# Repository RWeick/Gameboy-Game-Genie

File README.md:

# Gameboy-Game-Genie
The Kicad files and rom dump of the Gameboy Game Genie by Galoob. This includes the additional PCBs for the buttons and the LED.

In the replacement board folder, you will find a version of the PCB that uses an Atmel AT27C256 (or chip of compatible size and pinout) to replace the chip blob. This enables anyone with a damaged PCB to restore the system. It has been tested.

PCB Thicknesses: 0.8 mm

Replacement Board:

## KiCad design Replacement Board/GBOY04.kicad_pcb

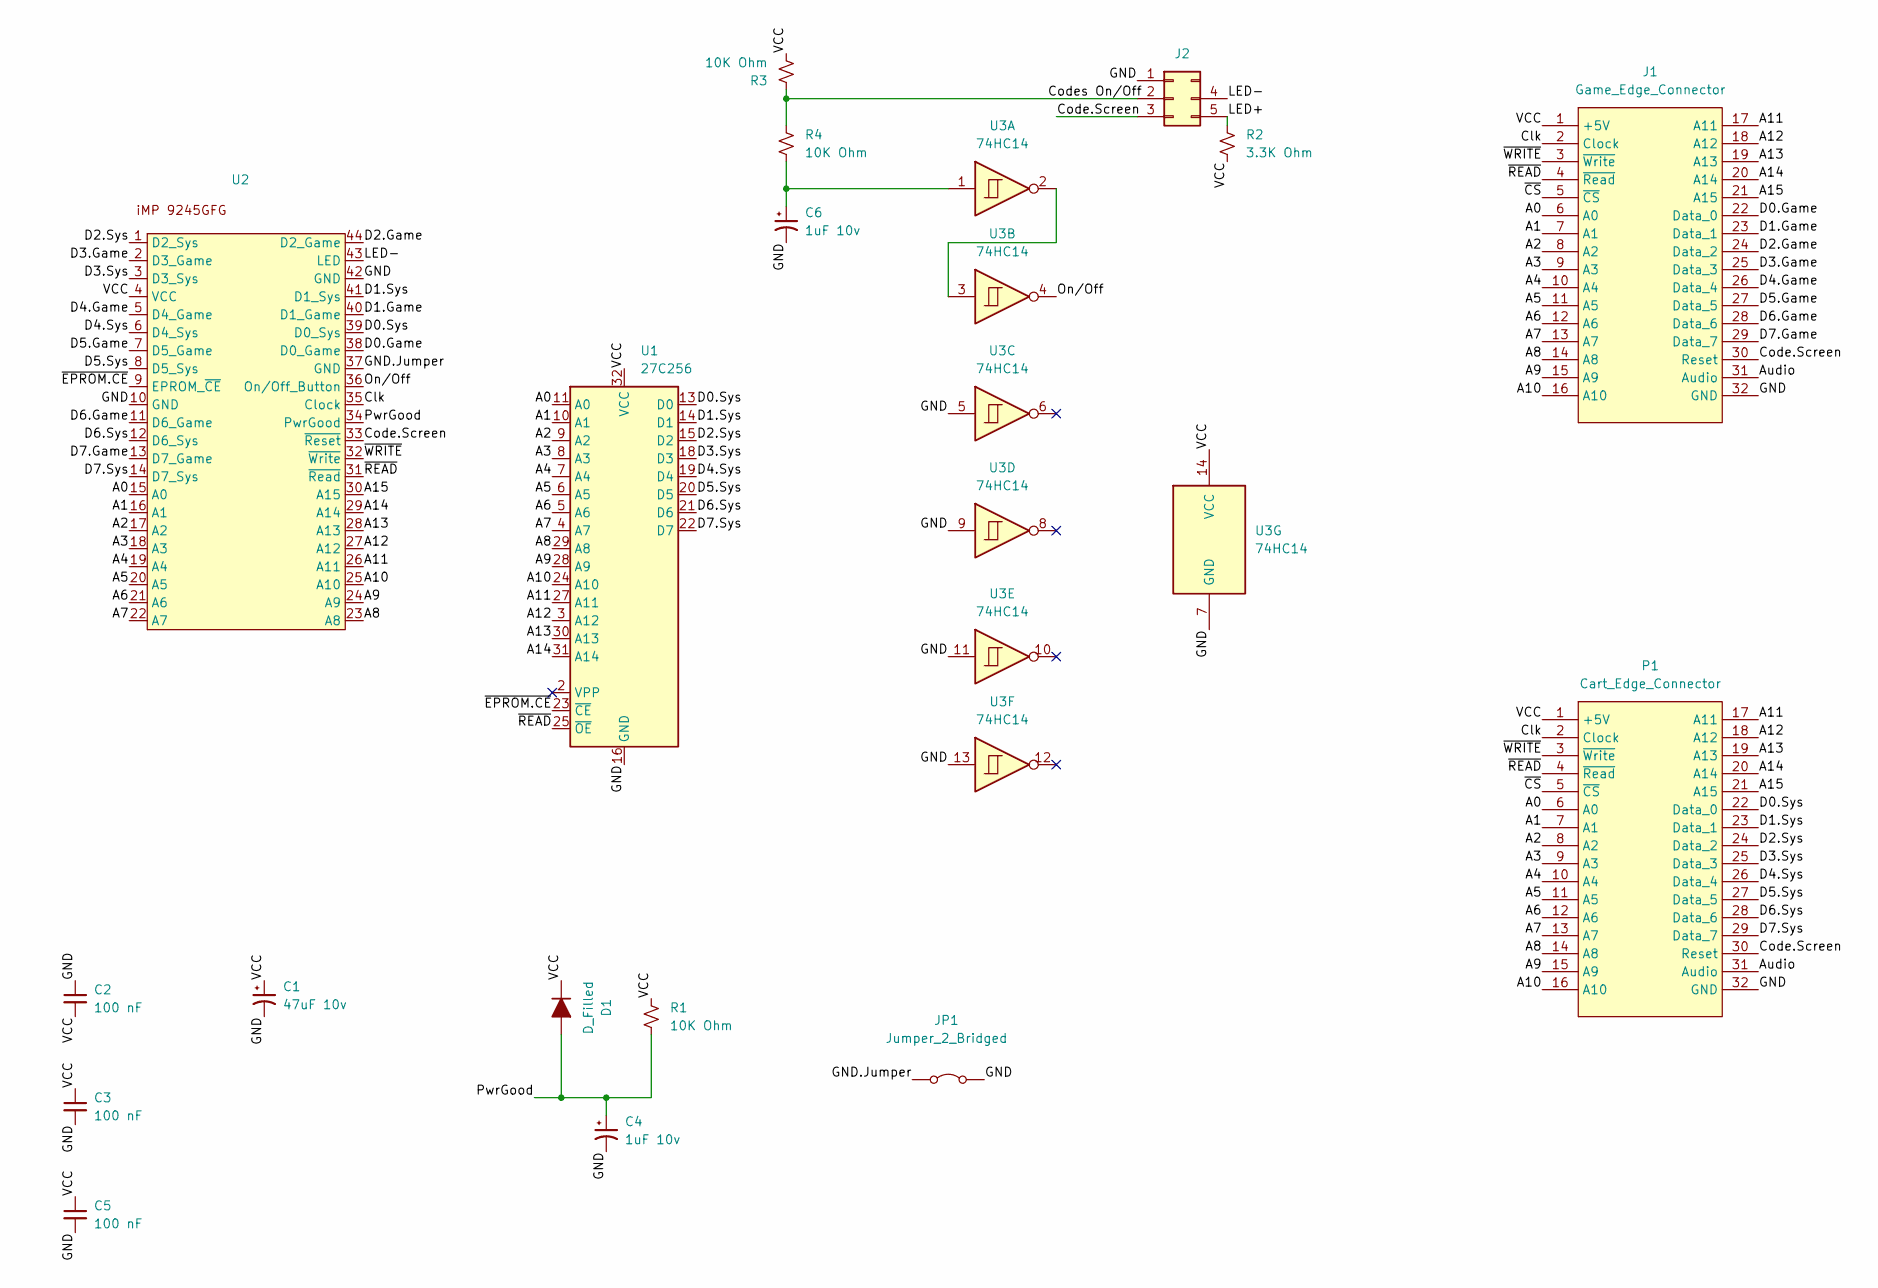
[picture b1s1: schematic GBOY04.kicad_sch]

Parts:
C1: 47uF 10v; C_Radial_D6.3mm_H5.0mm_P2.50mm
C2, C5: 100 nF; C_Disc_D5.0mm_W2.5mm_P5.00mm
C3: 100 nF; C_1206_3216Metric_Pad1.33x1.80mm_HandSolder
C4, C6: 1uF 10v; C_Disc_D3.8mm_W2.6mm_P2.50mm
D1: D_Filled; D_DO-35_SOD27_P7.62mm_Horizontal
J1: Game_Edge_Connector; Cartridge Connector
J2: Conn_02x03_Counter_Clockwise; PinHeader_2x03_P2.54mm_Vertical
JP1: Jumper_2_Bridged; SolderJumper-2_P1.3mm_Open_RoundedPad1.0x1.5mm
P1: Cart_Edge_Connector; Edge Connector
R1, R3, R4: 10K Ohm; R_Axial_DIN0204_L3.6mm_D1.6mm_P7.62mm_Horizontal
R2: 3.3K Ohm; R_Axial_DIN0204_L3.6mm_D1.6mm_P7.62mm_Horizontal
U1: 27C256; EPROM
U2: iMP PLD
U3: 74HC14; DIP-14_W7.62mm

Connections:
/A0: J1.6 (A0), P1.6 (A0), U1.11 (A0), U2.15 (A0)
/A1: J1.7 (A1), P1.7 (A1), U1.10 (A1), U2.16 (A1)
/A2: J1.8 (A2), P1.8 (A2), U1.9 (A2), U2.17 (A2)
/A3: J1.9 (A3), P1.9 (A3), U1.8 (A3), U2.18 (A3)
/A4: J1.10 (A4), P1.10 (A4), U1.7 (A4), U2.19 (A4)
/A5: J1.11 (A5), P1.11 (A5), U1.6 (A5), U2.20 (A5)
/A6: J1.12 (A6), P1.12 (A6), U1.5 (A6), U2.21 (A6)
/A7: J1.13 (A7), P1.13 (A7), U1.4 (A7), U2.22 (A7)
/A8: J1.14 (A8), P1.14 (A8), U1.29 (A8), U2.23 (A8)
/A9: J1.15 (A9), P1.15 (A9), U1.28 (A9), U2.24 (A9)
/A10: J1.16 (A10), P1.16 (A10), U1.24 (A10), U2.25 (A10)
/A11: J1.17 (A11), P1.17 (A11), U1.27 (A11), U2.26 (A11)
/A12: J1.18 (A12), P1.18 (A12), U1.3 (A12), U2.27 (A12)
/A13: J1.19 (A13), P1.19 (A13), U1.30 (A13), U2.28 (A13)
/A14: J1.20 (A14), P1.20 (A14), U1.31 (A14), U2.29 (A14)
/A15: J1.21 (A15), P1.21 (A15), U2.30 (A15)
/Audio: J1.31 (Audio), P1.31 (Audio)
/Clk: J1.2 (Clock), P1.2 (Clock), U2.35 (Clock)
/Code.Screen: J1.30 (Reset), J2.3, P1.30 (Reset), U2.33 (~Reset)
/Codes On/Off: J2.2, R3.1, R4.1
/D0.Game: J1.22 (Data_0), U2.38 (D0_Game)
/D0.Sys: P1.22 (Data_0), U1.13 (D0), U2.39 (D0_Sys)
/D1.Game: J1.23 (Data_1), U2.40 (D1_Game)
/D1.Sys: P1.23 (Data_1), U1.14 (D1), U2.41 (D1_Sys)
/D2.Game: J1.24 (Data_2), U2.44 (D2_Game)
/D2.Sys: P1.24 (Data_2), U1.15 (D2), U2.1 (D2_Sys)
/D3.Game: J1.25 (Data_3), U2.2 (D3_Game)
/D3.Sys: P1.25 (Data_3), U1.18 (D3), U2.3 (D3_Sys)
/D4.Game: J1.26 (Data_4), U2.5 (D4_Game)
/D4.Sys: P1.26 (Data_4), U1.19 (D4), U2.6 (D4_Sys)
/D5.Game: J1.27 (Data_5), U2.7 (D5_Game)
/D5.Sys: P1.27 (Data_5), U1.20 (D5), U2.8 (D5_Sys)
/D6.Game: J1.28 (Data_6), U2.11 (D6_Game)
/D6.Sys: P1.28 (Data_6), U1.21 (D6), U2.12 (D6_Sys)
/D7.Game: J1.29 (Data_7), U2.13 (D7_Game)
/D7.Sys: P1.29 (Data_7), U1.22 (D7), U2.14 (D7_Sys)
/GND: C1.2, C2.1, C3.2, C4.2, C5.2, C6.2, J1.32 (GND), J2.1, JP1.2 (B), P1.32 (GND), U1.16 (GND), U2.10 (GND), U2.42 (GND), U3.5, U3.7 (GND), U3.9, U3.11, U3.13
/GND.Jumper: JP1.1 (A), U2.37 (GND)
/LED+: J2.5, R2.1
/LED-: J2.4, U2.43 (LED)
/On/Off: U2.36 (On/Off_Button), U3.4
/PwrGood: C4.1, D1.2 (A), R1.2, U2.34 (PwrGood)
/VCC: C1.1, C2.2, C3.1, C5.1, D1.1 (K), J1.1 (+5V), P1.1 (+5V), R1.1, R2.2, R3.2, U1.32 (VCC), U2.4 (VCC), U3.14 (VCC)
/~CS: J1.5 (~CS), P1.5 (~CS)
/~EPROM.CE: U1.23 (~CE), U2.9 (EPROM_~CE)
/~READ: J1.4 (~Read), P1.4 (~Read), U1.25 (~OE), U2.31 (~Read)
/~WRITE: J1.3 (~Write), P1.3 (~Write), U2.32 (~Write)
unnamed: C6.1, R4.2, U3.1
unnamed: U3.2, U3.3

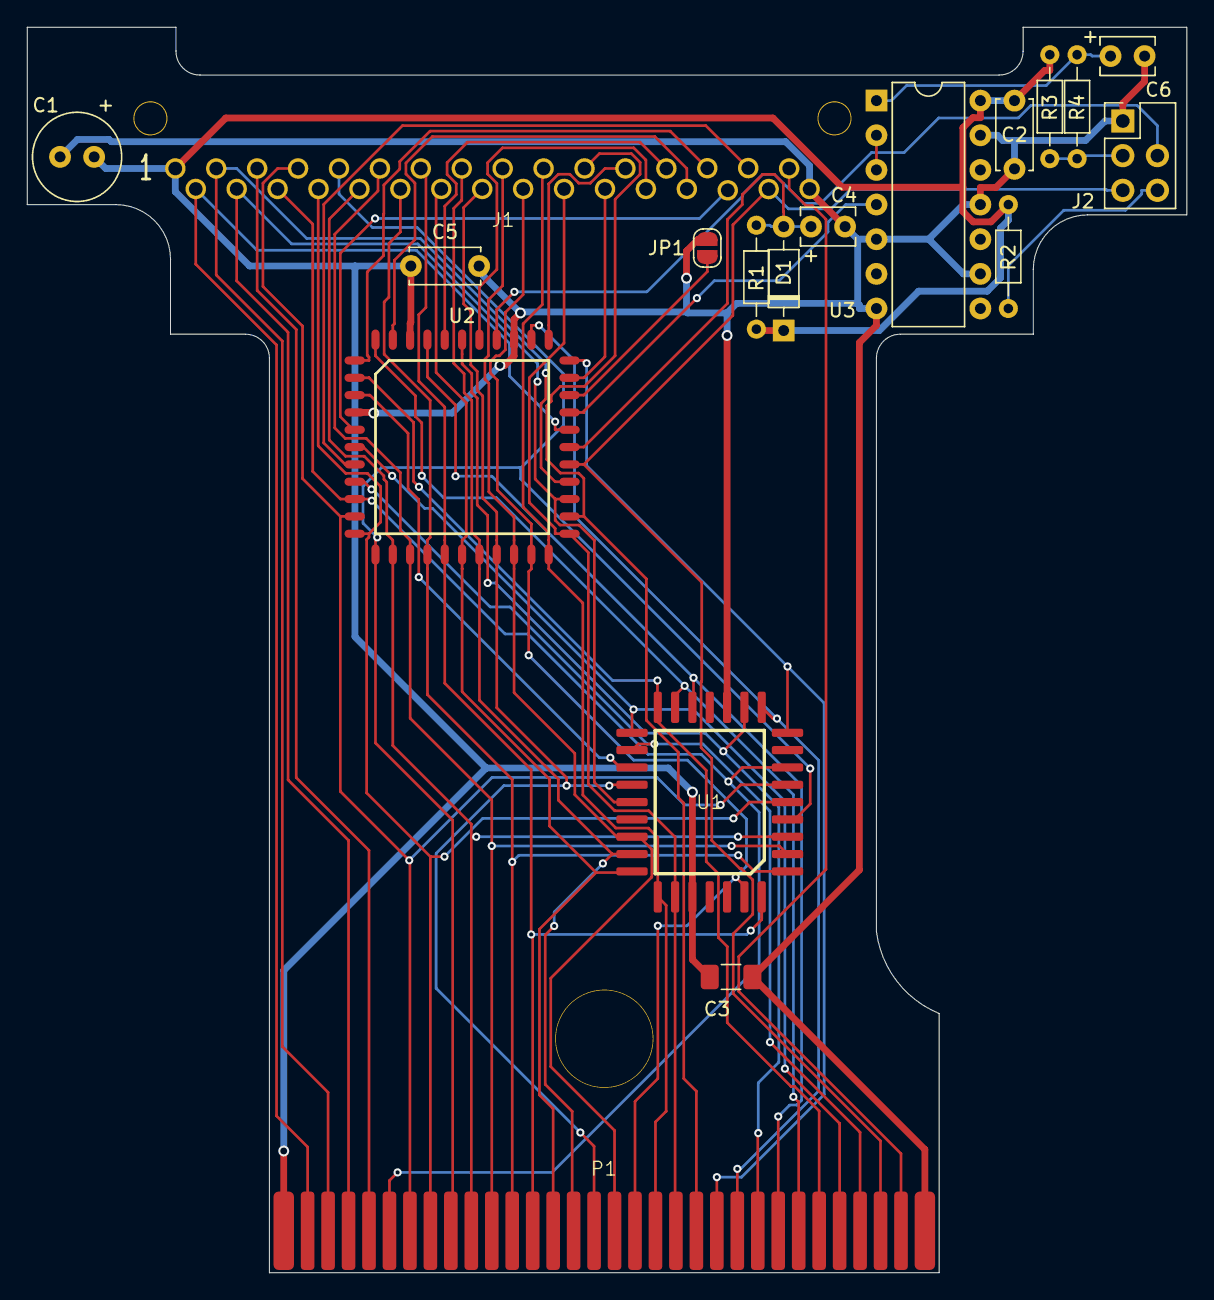
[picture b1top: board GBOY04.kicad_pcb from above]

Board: 2 copper layers, 85.0 x 91.3 mm, 19 parts (0 on the bottom side), 49 nets.

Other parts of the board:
Hole: Drill Hole

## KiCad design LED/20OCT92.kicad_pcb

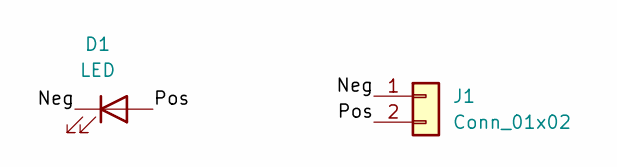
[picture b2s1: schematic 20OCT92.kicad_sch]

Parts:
D1: LED; LED_D4.0mm
J1: Conn_01x02; PinHeader_1x02_P2.54mm_Vertical

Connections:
/Neg: D1.1 (K), J1.1
/Pos: D1.2 (A), J1.2

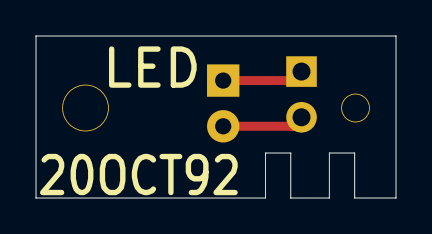
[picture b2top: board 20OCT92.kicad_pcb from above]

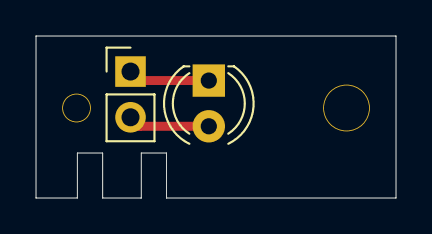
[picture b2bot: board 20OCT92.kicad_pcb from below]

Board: 2 copper layers, 20.0 x 9.0 mm, 3 parts (2 on the bottom side), 2 nets.

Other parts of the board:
Hole: Drill Holes

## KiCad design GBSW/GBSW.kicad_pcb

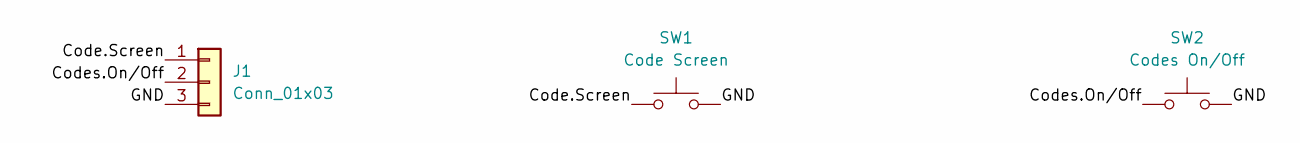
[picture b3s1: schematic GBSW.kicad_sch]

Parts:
J1: Conn_01x03; Wires
SW1: Code Screen; Buttons
SW2: Codes On/Off; Buttons

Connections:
/Code.Screen: J1.1, SW1.1
/Codes.On/Off: J1.2, SW2.1
/GND: J1.3, SW1.2, SW2.2

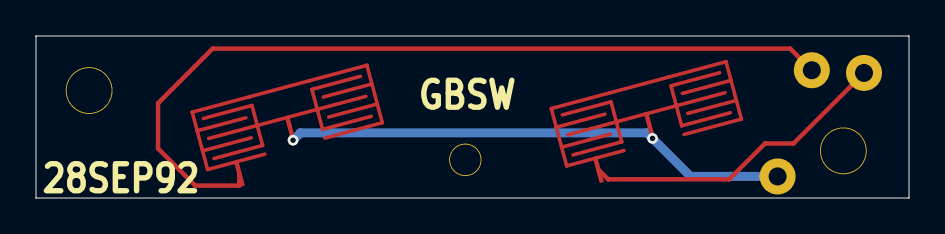
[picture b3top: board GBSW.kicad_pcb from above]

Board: 2 copper layers, 48.5 x 9.0 mm, 4 parts (0 on the bottom side), 3 nets.

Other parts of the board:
Holes: Drill Holes
